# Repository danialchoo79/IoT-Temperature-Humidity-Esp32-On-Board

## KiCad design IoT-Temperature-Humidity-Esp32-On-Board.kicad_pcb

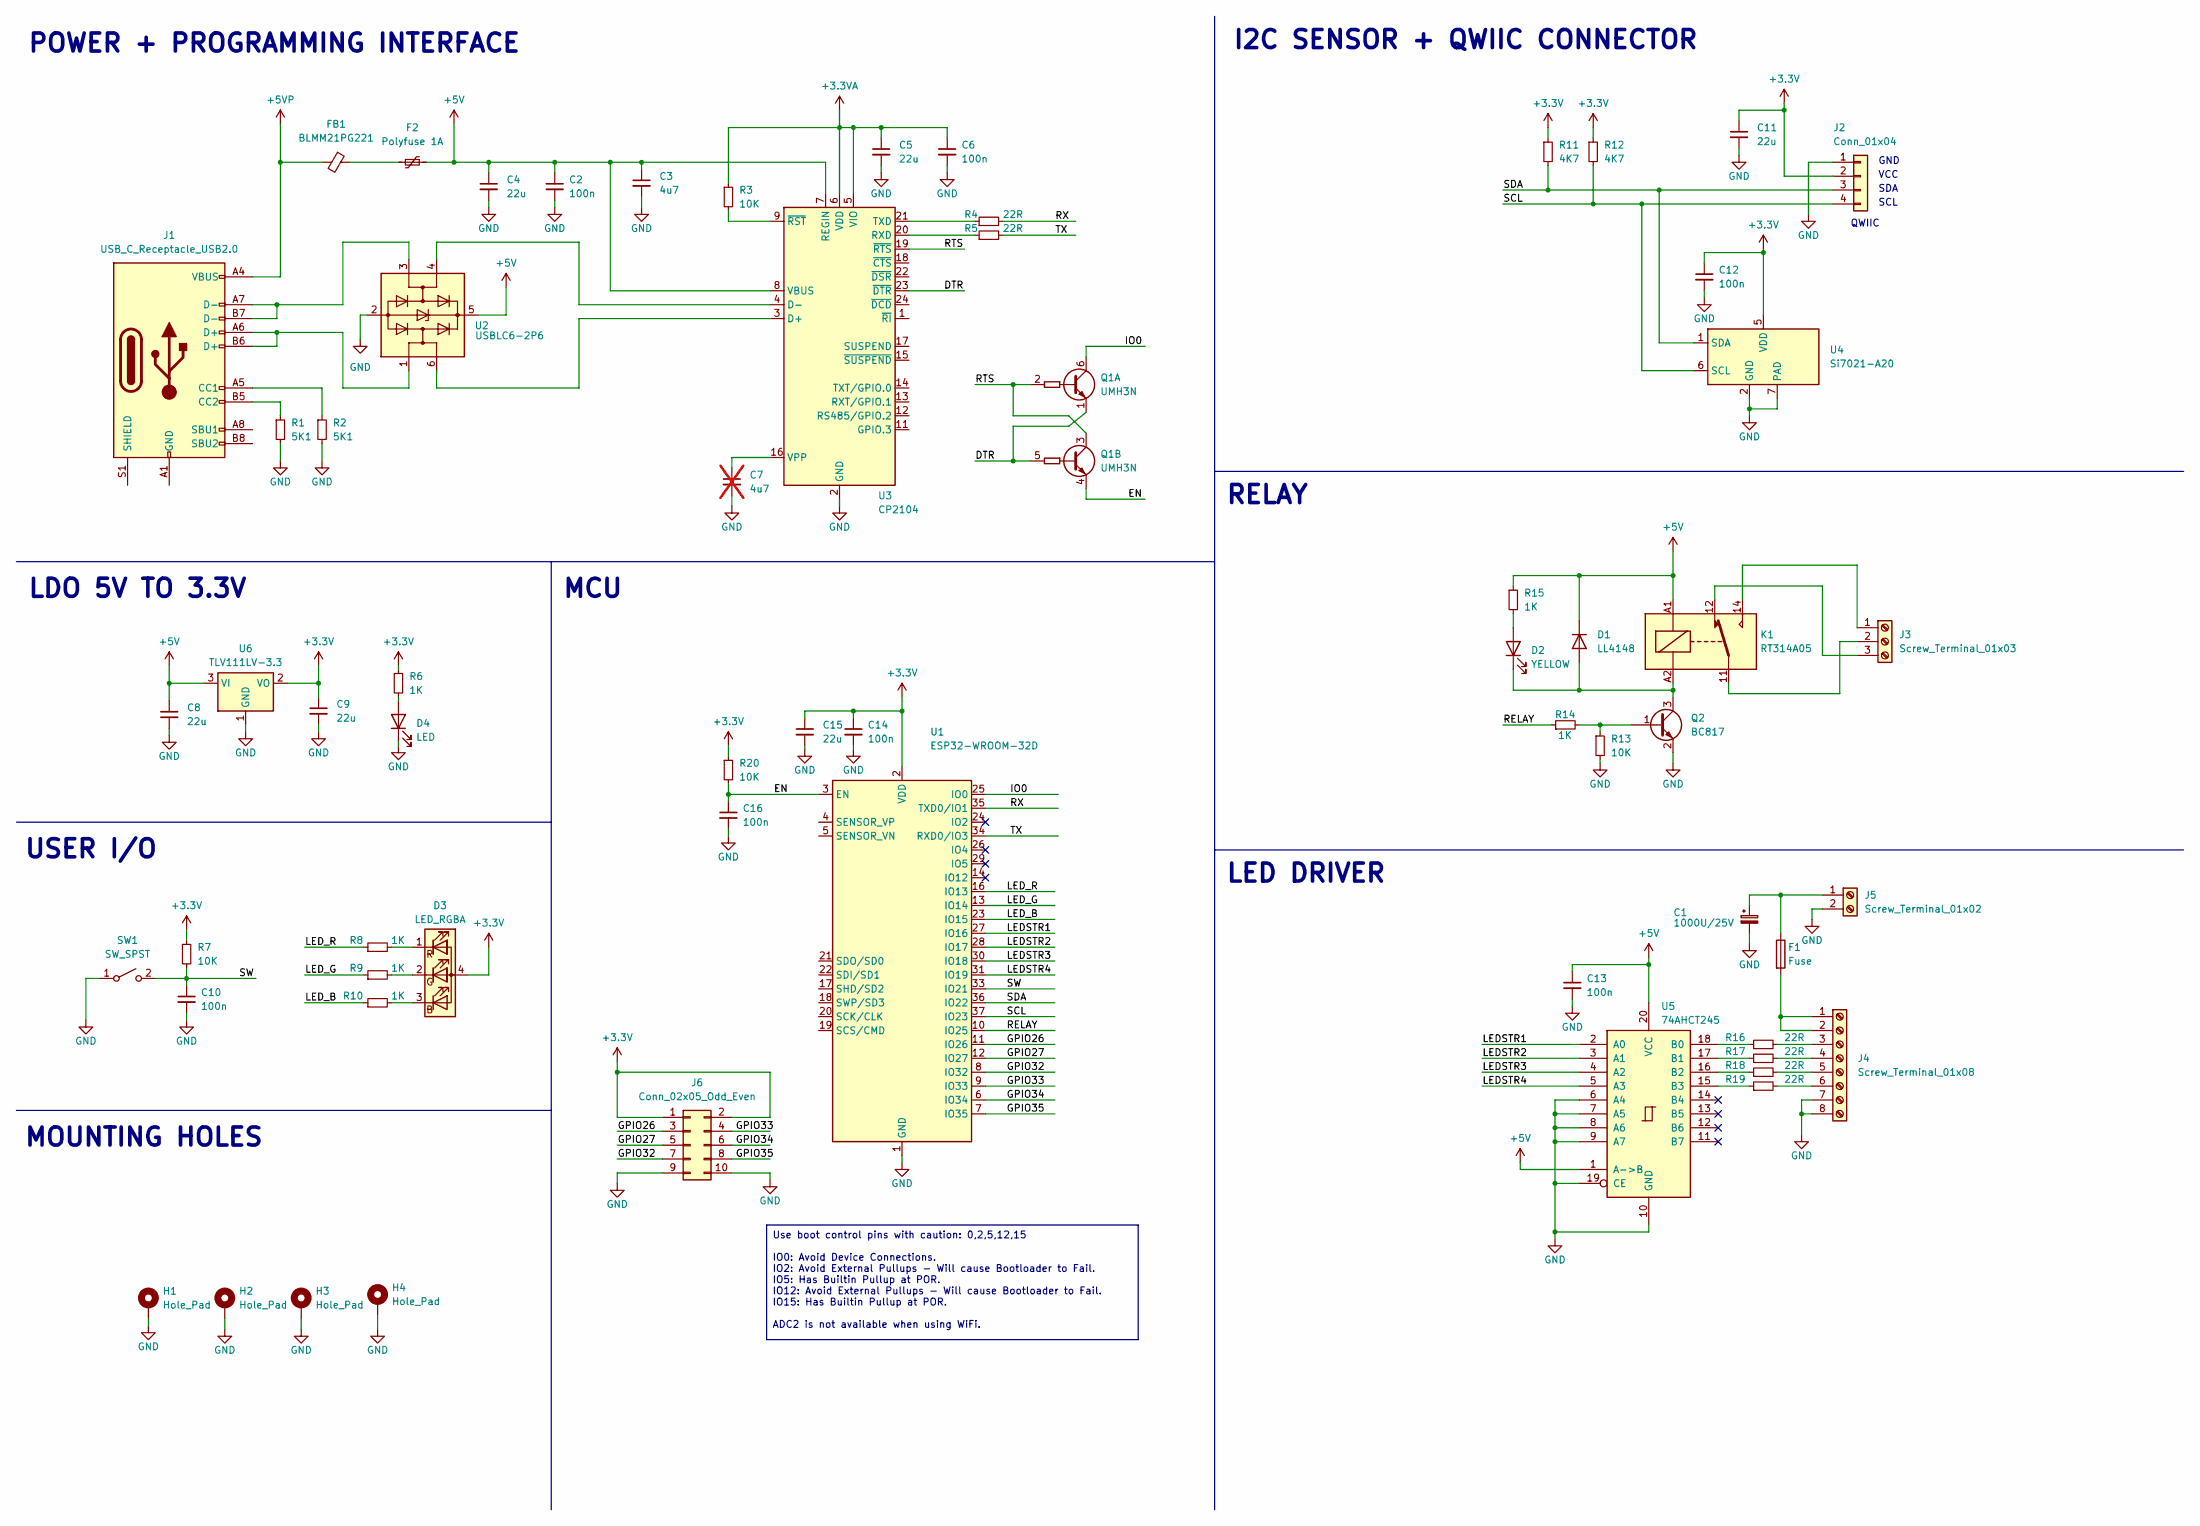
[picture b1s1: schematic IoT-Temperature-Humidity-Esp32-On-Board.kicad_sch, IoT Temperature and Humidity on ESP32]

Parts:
C1: 1000U/25V; CP_Radial_D10.0mm_P5.00mm
C2, C6, C10, C12, C13, C14, C16: 100n; C_0402_1005Metric_Pad0.74x0.62mm_HandSolder
C3: 4u7; C_0805_2012Metric_Pad1.18x1.45mm_HandSolder
C4, C5, C8, C9, C11, C15: 22u; C_0805_2012Metric_Pad1.18x1.45mm_HandSolder
C7: 4u7; C_0805_2012Metric_Pad1.18x1.45mm_HandSolder; not fitted
D1: LL4148; D_MiniMELF
D2: YELLOW; LED_0603_1608Metric_Pad1.05x0.95mm_HandSolder
D3: LED_RGBA; LED_RGB_Wuerth-PLCC4_3.2x2.8mm_150141M173100
D4: LED; LED_0603_1608Metric_Pad1.05x0.95mm_HandSolder
F1: Fuse; CONN2_03002_WRE
F2: Polyfuse 1A; Fuse_1206_3216Metric_Pad1.42x1.75mm_HandSolder
FB1: BLMM21PG221; L_0603_1608Metric_Pad1.05x0.95mm_HandSolder
H1, H2, H3, H4: Hole_Pad; MountingHole_3.2mm_M3_Pad_Via
J1: USB_C_Receptacle_USB2.0; USB_C_Receptacle_HRO_TYPE-C-31-M-12
J2: Conn_01x04; JST_SH_SM04B-SRSS-TB_1x04-1MP_P1.00mm_Horizontal
J3: Screw_Terminal_01x03; TerminalBlock_Phoenix_MKDS-1,5-3-5.08_1x03_P5.08mm_Horizont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
J4: Screw_Terminal_01x08; TerminalBlock_Phoenix_MKDS-1,5-8-5.08_1x08_P5.08mm_Horizont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
J5: Screw_Terminal_01x02; TerminalBlock_Phoenix_MKDS-1,5-2-5.08_1x02_P5.08mm_Horizont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
J6: Conn_02x05_Odd_Even; PinHeader_2x05_P2.54mm_Vertical
K1: RT314A05; Relay_SPDT_Schrack-RT1-16A-FormC_RM5mm
Q1: UMH3N; SOT-363_SC-70-6
Q2: BC817; SOT-23
R1, R2: 5K1; R_0402_1005Metric_Pad0.72x0.64mm_HandSolder
R3, R7, R13, R20: 10K; R_0402_1005Metric_Pad0.72x0.64mm_HandSolder
R4, R5, R16, R17, R18, R19: 22R; R_0402_1005Metric_Pad0.72x0.64mm_HandSolder
R6, R8, R9, R10, R14, R15: 1K; R_0402_1005Metric_Pad0.72x0.64mm_HandSolder
R11, R12: 4K7; R_0402_1005Metric_Pad0.72x0.64mm_HandSolder
SW1: SW_SPST; SW_Push_1P1T_NO_6x6mm_H9.5mm
U1: ESP32-WROOM-32D
U2: USBLC6-2P6; SOT-666
U3: CP2104; QFN-24-1EP_4x4mm_P0.5mm_EP2.6x2.6mm
U4: Si7021-A20; DFN-6-1EP_3x3mm_P1mm_EP1.5x2.4mm
U5: 74AHCT245; DIP-20_W7.62mm
U6: TLV111LV-3.3; SOT-223-3_TabPin2

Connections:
+3.3V: C9.1, C11.1, C12.1, C14.1, C15.1, D3.4 (A), J2.2, J6.1, J6.2, R6.1, R7.1, R11.1, R12.1, R20.1, U1.2 (VDD), U4.5 (VDD), U6.2 (VO)
+3.3VA: C5.1, C6.1, R3.1, U3.5 (VIO), U3.6 (VDD)
+5VP: FB1.2, J1.A4 (VBUS), J1.A9 (VBUS), J1.B4 (VBUS), J1.B9 (VBUS)
/DTR: Q1.1 (E1), Q1.5 (B2), U3.23 (~DTR)
/EN: C16.1, Q1.4 (E2), R20.2, U1.3 (EN)
/GPIO26: J6.3, U1.11 (IO26)
/GPIO27: J6.5, U1.12 (IO27)
/GPIO32: J6.7, U1.8 (IO32)
/GPIO33: J6.4, U1.9 (IO33)
/GPIO34: J6.6, U1.6 (IO34)
/GPIO35: J6.8, U1.7 (IO35)
/IO0: Q1.6 (C1), U1.25 (IO0)
/LEDSTR1: U1.27 (IO16), U5.2 (A0)
/LEDSTR2: U1.28 (IO17), U5.3 (A1)
/LEDSTR3: U1.30 (IO18), U5.4 (A2)
/LEDSTR4: U1.31 (IO19), U5.5 (A3)
/LED_B: R10.1, U1.23 (IO15)
/LED_G: R9.1, U1.13 (IO14)
/LED_R: R8.1, U1.16 (IO13)
/RELAY: R14.1, U1.10 (IO25)
/RTS: Q1.2 (B1), Q1.3 (C2), U3.19 (~RTS)
/RX: R4.2, U1.35 (TXD0/IO1)
/SCL: J2.4, R12.2, U1.37 (IO23), U4.6 (SCL)
/SDA: J2.3, R11.2, U1.36 (IO22), U4.1 (SDA)
/SW: C10.1, R7.2, SW1.2 (B), U1.33 (IO21)
/TX: R5.2, U1.34 (RXD0/IO3)
GND: C1.2, C2.2, C3.2, C4.2, C5.2, C6.2, C7.2, C8.2, C9.2, C10.2, C11.2, C12.2, C13.2, C14.2, C15.2, C16.2, D4.1 (K), H1.1, H2.1, H3.1, H4.1, J2.1, J4.7, J4.8, J5.2, J6.9, J6.10, Q2.2 (E), R1.2, R2.2, R13.2, SW1.1 (A), U1.1 (GND), U1.15 (GND), U1.38 (GND), U1.39 (GND), U2.2 (GND), U3.2 (GND), U3.25 (GND), U4.2 (GND), U4.7 (PAD), U5.6 (A4), U5.7 (A5), U5.8 (A6), U5.9 (A7), U5.10 (GND), U5.19 (CE), U6.1 (GND)
unnamed: D1.2 (A), D2.1 (K), K1.A2, Q2.3 (C)
unnamed: D2.2 (A), R15.2
unnamed: D3.3 (BK), R10.2
unnamed: D3.2 (GK), R9.2
unnamed: D3.1 (RK), R8.2
unnamed: D4.2 (A), R6.2
unnamed: F2.2, FB1.1
unnamed: J1.A5 (CC1), R2.1
unnamed: J1.B5 (CC2), R1.1
unnamed: J1.A7 (D-), J1.B7 (D-), U2.3 (I/O2)
unnamed: J1.A1 (GND), J1.A12 (GND), J1.B1 (GND), J1.B12 (GND)
unnamed: J3.1, K1.14
unnamed: J3.2, K1.11
unnamed: J3.3, K1.12
unnamed: F1.2, J4.1, J4.2
unnamed: J4.3, R16.2
unnamed: J4.4, R17.2
unnamed: J4.5, R18.2
unnamed: J4.6, R19.2
unnamed: C1.1, F1.1, J5.1
unnamed: Q2.1 (B), R13.1, R14.2
unnamed: U2.6 (I/O1), U3.3 (D+)
unnamed: U2.4 (I/O2), U3.4 (D-)
unnamed: R5.1, U3.20 (RXD)
unnamed: R4.1, U3.21 (TXD)
unnamed: C7.1, U3.16 (VPP)
unnamed: R3.2, U3.9 (~RST)
unnamed: R16.1, U5.18 (B0)
unnamed: R17.1, U5.17 (B1)
unnamed: R18.1, U5.16 (B2)
unnamed: R19.1, U5.15 (B3)

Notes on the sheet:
Use boot control pins with caution: 0,2,5,12,15 IO0: Avoid Device Connections. IO2: Avoid External Pullups - Will cause Bootloader to Fail. IO5: Has Builtin Pullup at POR. IO12: Avoid External Pullups - Will cause Bootloader to Fail. IO15: Has Builtin Pullup at POR. ADC2 is not available when using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
LED DRIVER
MOUNTING HOLES
USER I/O
POWER + PROGRAMMING INTERFACE
SCL
SDA
I2C SENSOR + QWIIC CONNECTOR
RELAY
VCC
GND
MCU
LDO 5V TO 3.3V
QWIIC

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
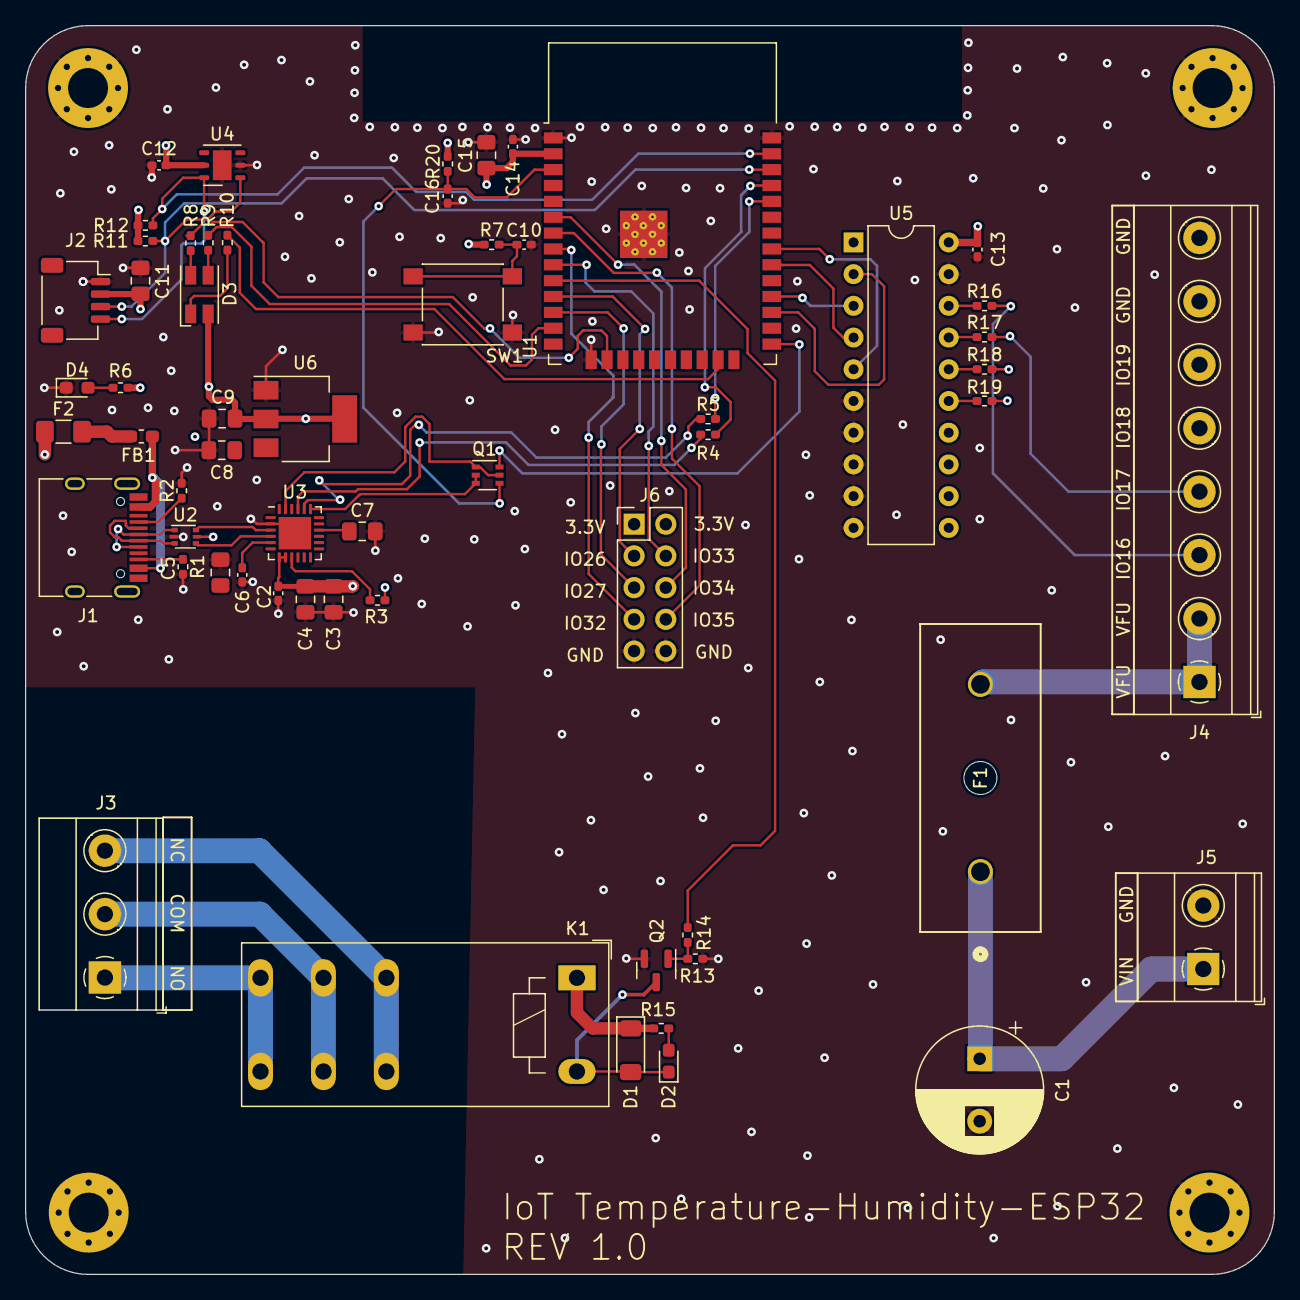
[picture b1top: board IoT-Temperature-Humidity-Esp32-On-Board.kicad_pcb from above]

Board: 4 copper layers, 100.0 x 100.0 mm, 63 parts (0 on the bottom side), 59 nets.

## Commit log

2024-07-13 README.md
    IoT Temperature Humidity Board using ESP32
